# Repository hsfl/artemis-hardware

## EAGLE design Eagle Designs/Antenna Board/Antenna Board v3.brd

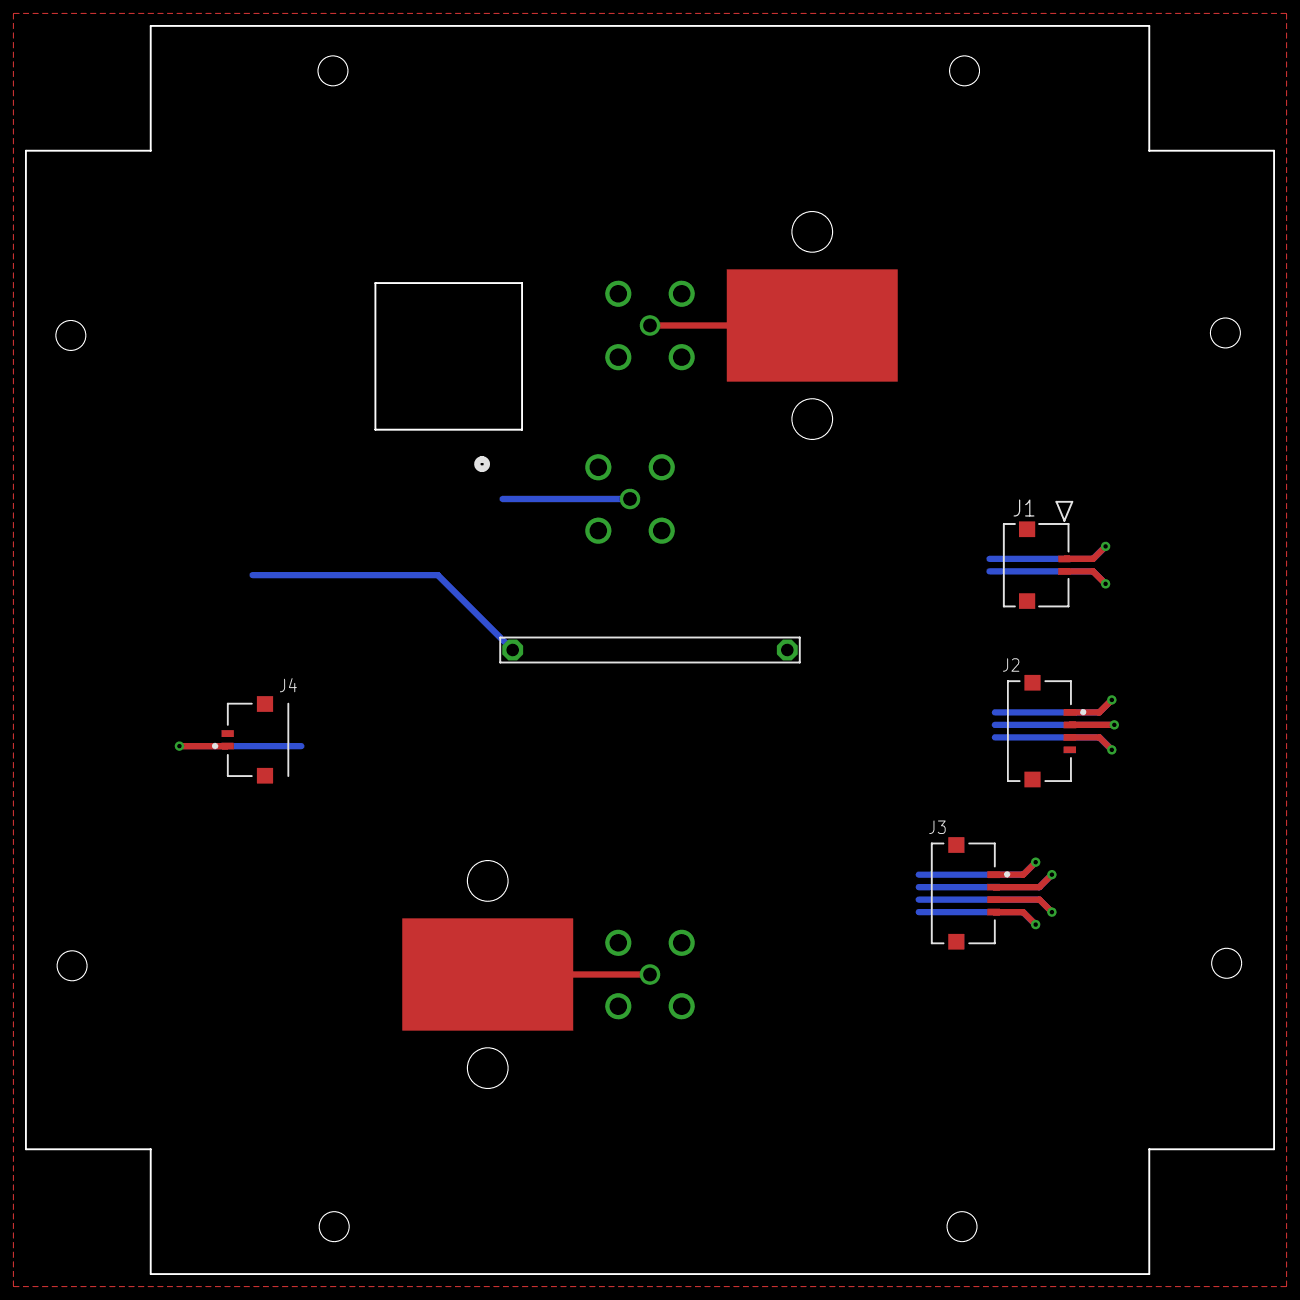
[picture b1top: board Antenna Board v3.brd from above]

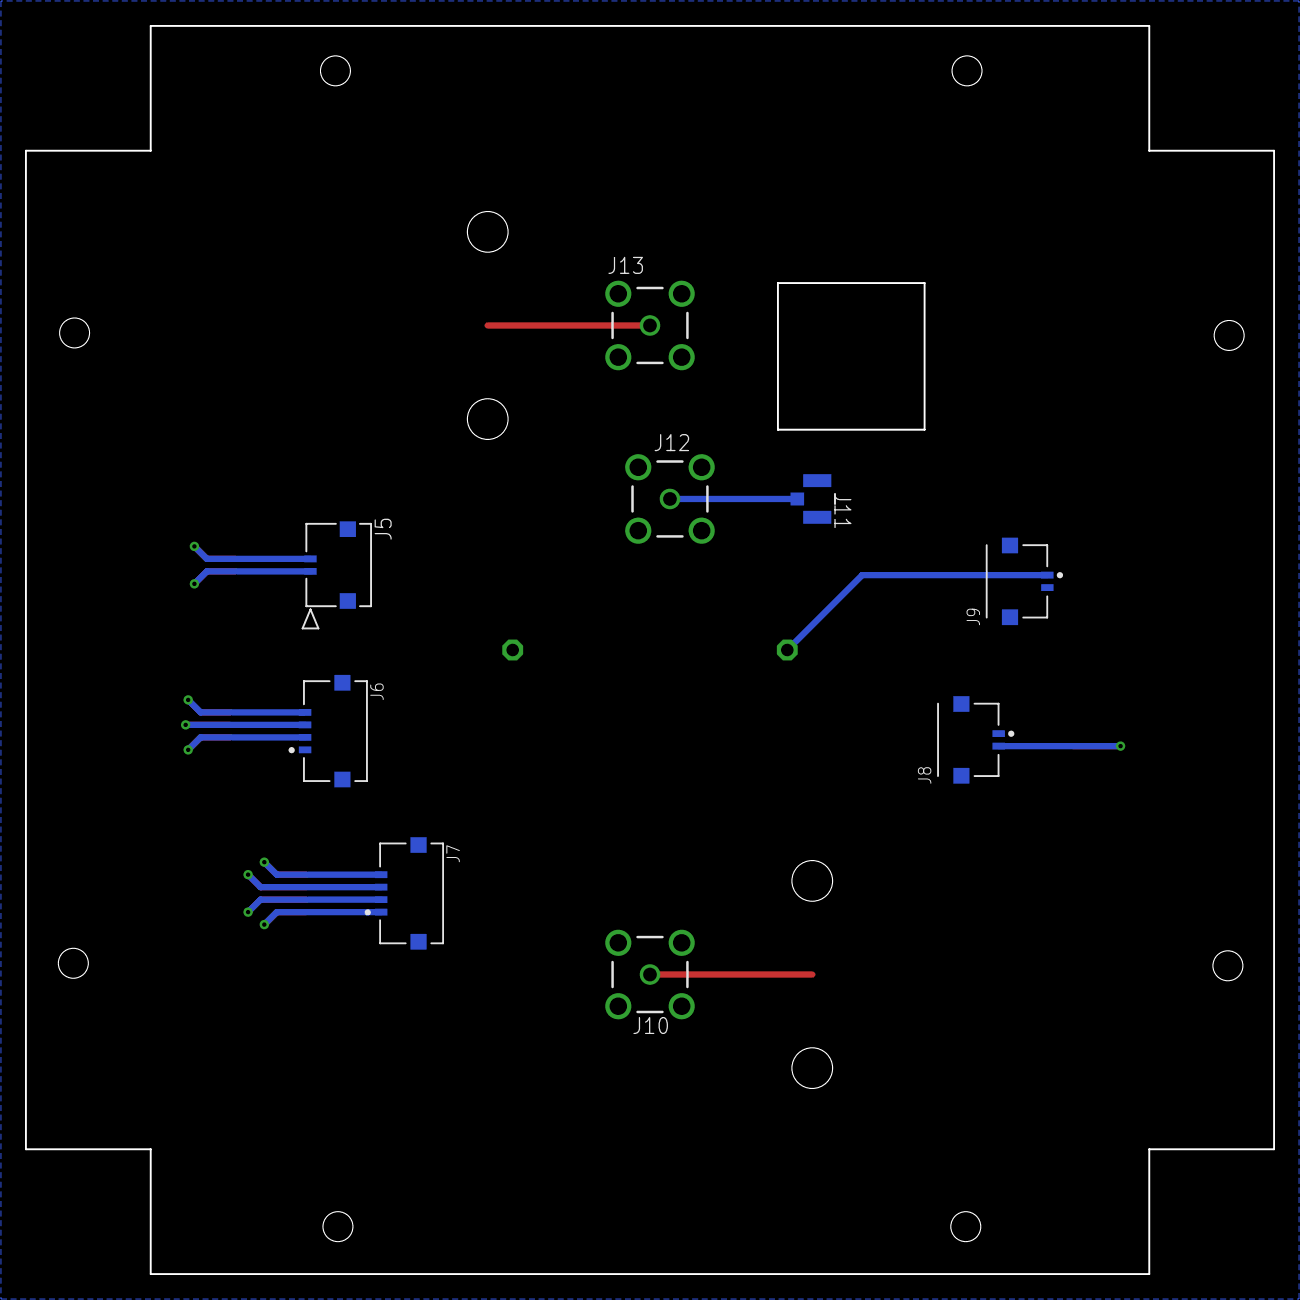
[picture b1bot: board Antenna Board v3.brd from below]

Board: 2 copper layers, 100.0 x 100.0 mm, 16 parts (9 on the bottom side), 15 nets.

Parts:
J1, J5: 5037630291; CON_5037630291
J2, J3, J6, J7: MOLEX_503763-0491MOLEX_503763-0491_0_0; MOLEX_503763-0491_0
J4, J8, J9: MOLEX_503763-0291MOLEX_503763-0291_0_0; MOLEX_503763-0291_0
J10, J12, J13: MCX-J-P-X-ST-TH1; SAMTEC_MCX-J-P-X-ST-TH1
J11: U.FL-R-SMT-1(01); CONN_-SMT-1(01)
U$1, U$2: ANTENNA_PAD
U$3: BURNWIRE

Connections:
ANTENNA1: J10.1, U$2.1
ANTENNA2: J13.1, U$1.1
GND: J1.3, J1.4, J2.4, J2.5, J2.6, J3.5, J3.6, J4.2, J4.3, J4.4, J5.3, J5.4, J6.1, J6.5, J6.6, J7.5, J7.6, J8.1, J8.3, J8.4, J9.2, J9.3, J9.4, J10.S1, J10.S2, J10.S3, J10.S4, J11.1, J11.2, J12.S1, J12.S2, J12.S3, J12.S4, J13.S1, J13.S2, J13.S3, J13.S4, U$3.2
ORION-SPACE: J11.3, J12.1
RBF1: J1.1, J5.2
RBF2: J1.2, J5.1
RX+: J3.1, J7.4
RX-: J3.2, J7.3
TCK: J2.3, J6.2
TMS: J2.2, J6.3
TX+: J3.3, J7.2
TX-: J3.4, J7.1
VCC_BATT: J4.1, J8.2
VCC_BURN: J9.1, U$3.1
VRTREF: J2.1, J6.4

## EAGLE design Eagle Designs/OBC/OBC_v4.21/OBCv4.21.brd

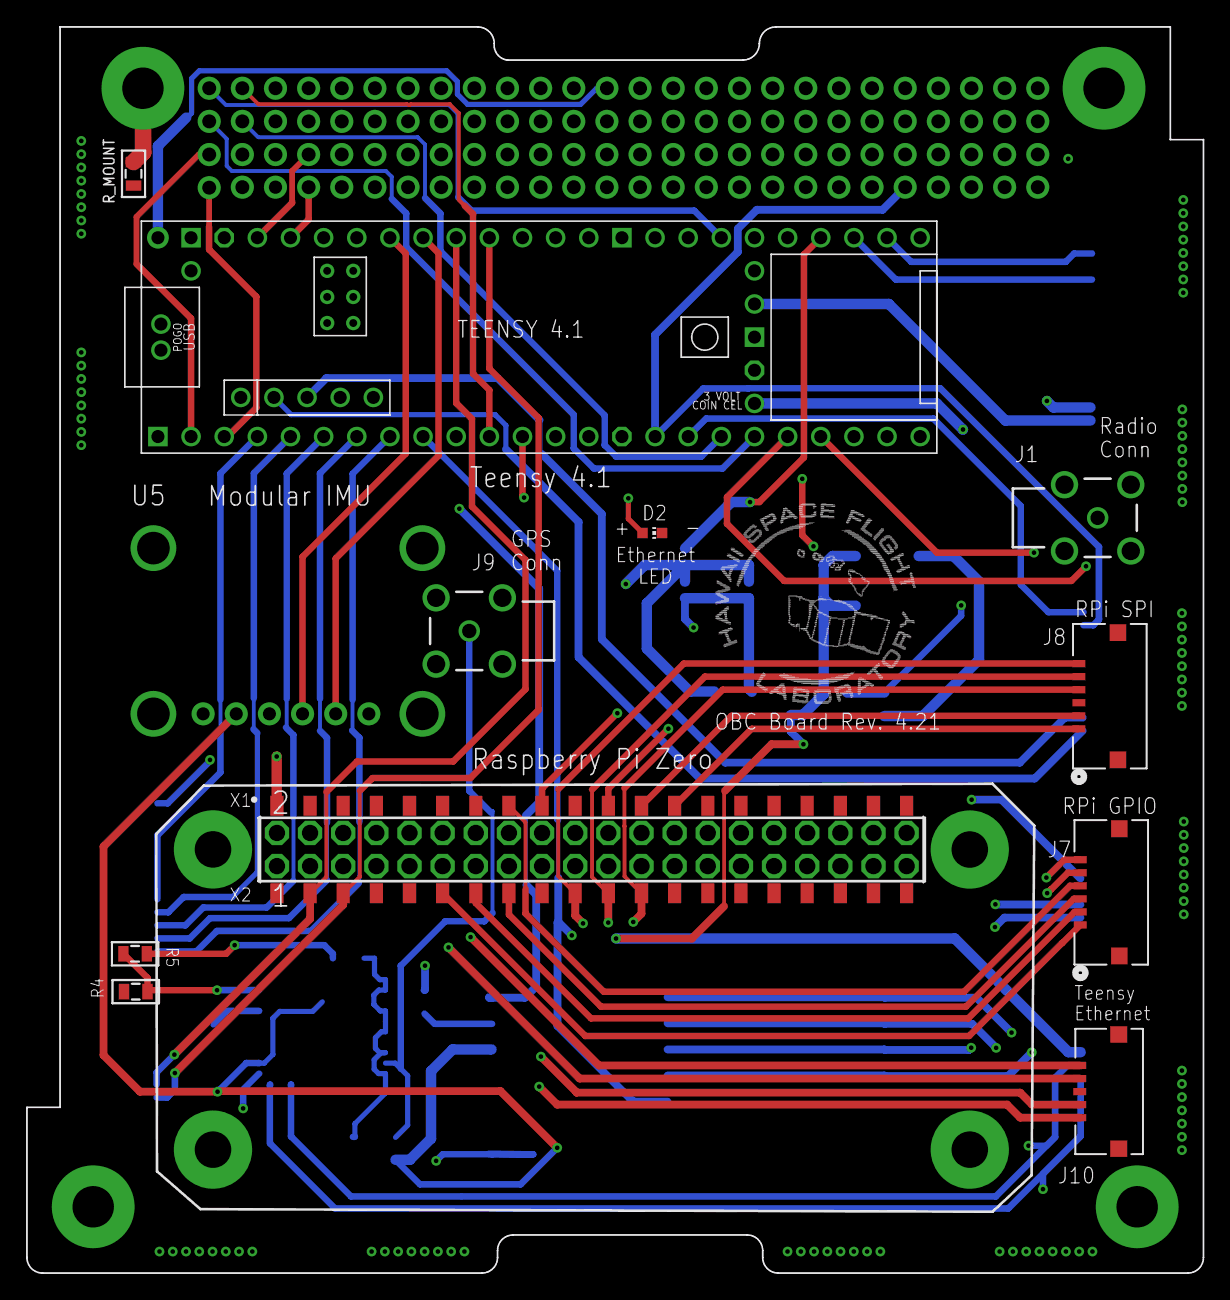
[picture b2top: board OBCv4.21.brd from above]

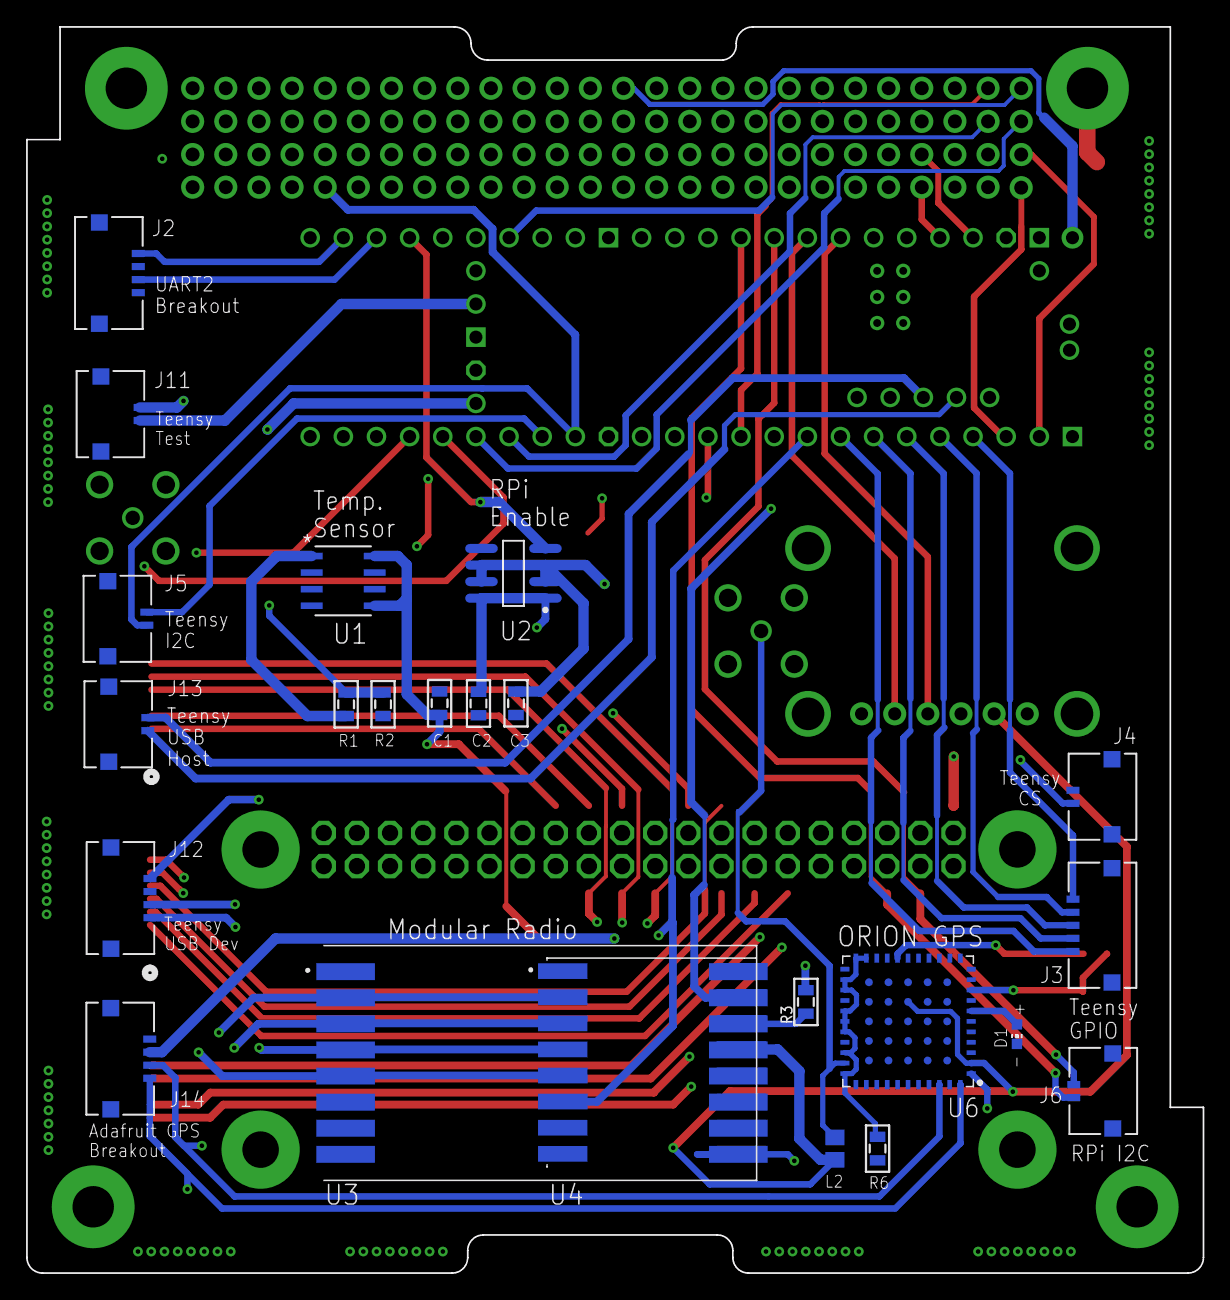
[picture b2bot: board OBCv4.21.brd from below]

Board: 4 copper layers, 90.2 x 95.5 mm, 37 parts (23 on the bottom side), 70 nets.

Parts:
C1: 0.1 uF; 0805
C2, C3: 1 uF; 0805
D1, D2: CHIP-LED0603
H1: PC104_WCONN
J1, J9: MCX-J-P-H-RA-TH1; SAMTEC_MCX-J-P-H-RA-TH1
J2, J12, J14: 5037630491; CON_5037630491
J3, J10: 5037630591; CON_5037630591
J4, J5, J6, J11, J13: 5037630291; CON_5037630291
J7: 503763-0691; CONN_503763-0691_MOL
J8: 5037630691; CONN_503763-0691_MOL
L2: AIMC-0805-2N2S-T; INDC2012X105N
R1: 45.3k; 0805
R2: 10k; 0805
R3, R4, R5, R6: 0; 0805
R_MOUNT: 1M; 0805
U1: TMP36FSZR_8_ADI-L; R_8_ADI-L
U2: LTC1477CS8LINEAR_TECHNOLOGY_LTC1477CS8_0_2; LINEAR_TECHNOLOGY_LTC1477CS8_2
U3: RFM23BP
U4: RFM69HCW
U5: 1X06_ROUND_70
U6: ORION_A38LORION_A38L; ORION_A38L
U$1: TEENSY41
X1: C25582-40G-M36-0A; ADAFRUIT_C25582-40G-M36-0A_0
X2: SSW-120-02-G-D

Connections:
3V3_BUS: H1.2.27, H1.2.28, R5.1, U6.18
5V_BUS: C3.1, H1.2.25, H1.2.26, U2.2, U2.3, U2.6, U2.7, U$1.+5V, U$1.VIN
+3V3_VCC: C1.1, J14.2, L2.1, U1.5, U1.8, U3.13, U4.13, U5.2, U6.2, U6.58, U$1.3V3-1, U$1.3V3-2, U$1.3V3-3
AIN0: R1.1, R2.2, U$1.14-A0/TX3/SPDIF_OUT
AIN1: H1.1.3, U$1.15-A1/RX3/SPDIF_IN
AIN2: H1.1.4, U$1.41-A17/MISO1
AIN3: H1.1.5, U$1.20-A6/TX5/LRCLK1
AIN4: H1.1.6, U$1.21-A7/RX5/BCLK1
AIN5: H1.1.7, U$1.22-A8/CTX1
AIN6: H1.1.8, U$1.23-A9/CRX1/MCLK1
ANT_CONN: J1.1, U3.9, U4.9
DIO1: U3.15, U4.15, U$1.8-TX2/IN1
ETH_RX+: J10.1, U$1.R+
ETH_RX-: J10.2, U$1.R-
ETH_TX+: J10.5, U$1.T+
ETH_TX-: J10.4, U$1.T-
GND: C1.2, C2.2, C3.2, D1.C, D2.C, H1.2.7, H1.2.14, H1.2.17, H1.2.21, H1.2.22, H1.2.29, H1.2.30, H1.2.32, H1.2.47, H1.2.48, J1.S1, J1.S2, J1.S3, J1.S4, J2.2, J2.4, J2.5, J2.6, J3.6, J3.7, J4.2, J4.3, J4.4, J5.3, J5.4, J6.3, J6.4, J7.7, J7.8, J8.3, J9.S1, J9.S2, J9.S3, J9.S4, J10.3, J10.6, J10.7, J11.3, J11.4, J12.2, J12.5, J12.6, J13.3, J13.4, J14.1, J14.5, J14.6, R2.1, R4.1, R6.2, R_MOUNT.2, U1.4, U2.5, U3.1, U3.8, U3.10, U4.1, U4.8, U4.10, U5.3, U6.10, U6.11, U6.15, U6.19, U6.64, U$1.G, U$1.GND1, U$1.GND2, U$1.GND3, U$1.GND4, U$1.GND5, U$1.GND6, X1.39
GPIO17: J7.1, X1.11
GPIO22: J7.3, X1.15
GPIO23: J7.4, X1.16
GPIO24: J7.5, X1.18
GPIO25: J7.6, X1.22
GPIO27: J7.2, X1.13
GPS_RSTN: U6.1, U$1.33-MCLK2
I2C1_SCL: H1.1.43, J5.2, U$1.24-A10/TX6/SCL2
I2C1_SDA: H1.1.41, J5.1, U$1.25-A11/RX6/SDA2
I2C2_SCL: U5.4, U$1.19-A5/SCL0
I2C2_SDA: U5.5, U$1.18-A4/SDA0
unnamed: D2.A, U$1.LED
unnamed: R3.1, U3.14
unnamed: R1.2, U1.1
unnamed: R4.2, R5.2, U6.9
unnamed: J9.1, L2.2, U6.32
unnamed: D1.A, U6.7
unnamed: H1.P$4, R_MOUNT.1
RADIO_RESET: R3.2, U4.6, U$1.7-RX2/OUT1A
RF_GND: R6.1, U6.21, U6.22, U6.24, U6.25, U6.27, U6.28, U6.29, U6.31, U6.33
RPI_5V_PWR_IN: C2.1, U2.1, U2.8, X1.2
RPI_ENABLE: U2.4, U$1.36-PWM
SCL1_I2C: J6.1, U$1.16-A2/RX4/SCL1, X1.5
SDA1_I2C: J6.2, U$1.17-A3/TX4/SDA1, X1.3
SPI0_CE0_N: J8.2, X1.24
SPI0_CE1_N: J8.1, X1.26
SPI0_MISO: J8.5, U$1.12-MISO/MQSL, X1.21
SPI0_MOSI: J8.6, U$1.11-MOSI/CTX1, X1.19
SPI0_SCLK: J8.4, U$1.13-SCK/LED, X1.23
SPI1_CS1: U3.5, U4.5, U$1.38-A14/CS/IN1
SPI1_D0: H1.2.2, U3.2, U4.2, U$1.39-A15/CS/OUT1A
SPI1_D1: H1.2.3, U3.3, U4.3, U$1.26-A12/MOSI1
SPI1_SCLK: H1.2.1, U3.4, U4.4, U$1.27-A13/SCK1
T_CS: J4.1, U$1.10-CS\MQSR
T_CS1: H1.2.4, U$1.9-OUT1C
T_GPIO2: J3.5, U$1.2-OUT2
T_GPIO3: J3.4, U$1.3-LRCLK2
T_GPIO4: J3.3, U$1.4-BCLK2
T_GPIO5: J3.2, U$1.5-IN2
T_GPIO6: J3.1, U$1.6-OUT1D
T_PROGRAM: J11.2, U$1.PROGRAM
T_VBAT: J11.1, U$1.VBAT
T_VUSB: J12.1, U$1.VUSB
UART2_RXD: J2.1, U$1.34-RX8
UART2_TXD: J2.3, U$1.35-TX8
UART4_RXD: H1.1.2, U$1.0-RX1/CS1/CRX2
UART4_TXD: H1.1.1, U$1.1-TX1/MISO1/CTX2
UART5_RXD: J14.3, U6.42, U$1.29-TX7
UART5_TXD: J14.4, U6.44, U$1.28-RX7
USB_DEV_D+: J12.4, U$1.D+
USB_DEV_D-: J12.3, U$1.D-
USB_HOST_D+: J13.1, U$1.DP
USB_HOST_D-: J13.2, U$1.DM

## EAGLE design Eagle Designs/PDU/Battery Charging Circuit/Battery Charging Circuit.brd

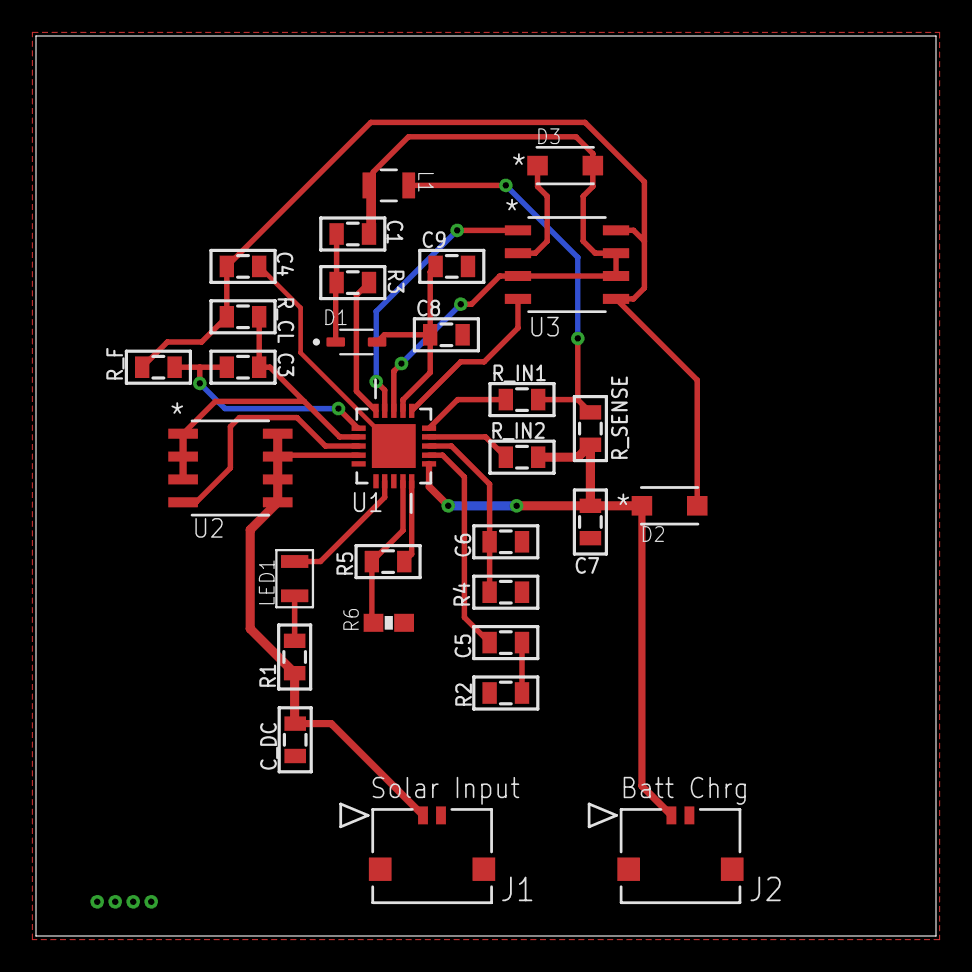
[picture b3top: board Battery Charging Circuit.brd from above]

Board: 2 copper layers, 50.0 x 50.0 mm, 30 parts (0 on the bottom side), 24 nets.

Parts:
C1, C3, C5: 0.1 uF; 0805
C4, C7: 10 uF; 0805
C6: 4.7 uF; 0805
C8, C9: 1 uF; 0805
C_DC: 0.1 uF; 0805
D1: CMDSH-3TR; SOD2512X110N
D2, D3: MBR230S1F; CR_0LSFT1G_ONS
J1, J2: 5037630291; CON_5037630291
L1: AIML-0805-150K-T; AIML-0805_ABR
LED1: LED_0805
R1: 3 k; 0805
R2: 6.04 k; 0805
R3: 0; 0805
R4: 26.7 k; 0805
R5: 169 k; 0805
R6: 28.4k; 0603-RES
R_CL: 1; 0805
R_F: 5.1 k; 0805
R_IN1, R_IN2: 3.01 k; 0805
R_SENSE: 1; 0805
U1: LTC4012IUFPBF; QFN50P400X400X80-21N
U2: SI4431BDY-T1-E3; SOIC-8_SI
U3: AO4818B; SOIC8_NARROW_VIS

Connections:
BATT_CHRG: C7.1, D2.1, J2.1, R_IN2.2, R_SENSE.1, U1.11
BGATE: U1.16, U3.4
CHRG: LED1.2, U1.7
GND: C4.2, C6.2, C7.2, C8.2, C9.2, C_DC.2, J1.2, J1.3, J1.4, J2.2, J2.3, J2.4, R2.1, R4.1, R6.1, U1.21
INFET: U1.3, U2.4
INH_SW1_NC: C_DC.1, J1.1, R1.2, U1.4, U2.5, U2.6, U2.7, U2.8
ITH: C5.1, U1.12
unnamed: LED1.1, R1.1
unnamed: C5.2, R2.2
unnamed: R3.1, U1.20
unnamed: C3.2, R_F.1, U1.1
unnamed: C8.1, C9.1, D1.A, U1.17
unnamed: C1.1, D1.C, R3.2
unnamed: R_IN1.1, U1.15
unnamed: R_IN2.1, U1.14
unnamed: C6.1, R4.2, U1.13
unnamed: R5.1, U1.10
unnamed: R5.2, R6.2, U1.9
R_SENSE_R_IN1: L1.1, R_IN1.2, R_SENSE.2
S2: D3.1, U3.2
SW: C1.2, D3.2, L1.2, U1.18, U3.3, U3.6, U3.7
TGATE: U1.19, U3.1
U2_S: C3.1, R_CL.1, U1.2, U2.1, U2.2, U2.3
VBATT: C4.1, D2.2, R_CL.2, R_F.2, U3.5, U3.8

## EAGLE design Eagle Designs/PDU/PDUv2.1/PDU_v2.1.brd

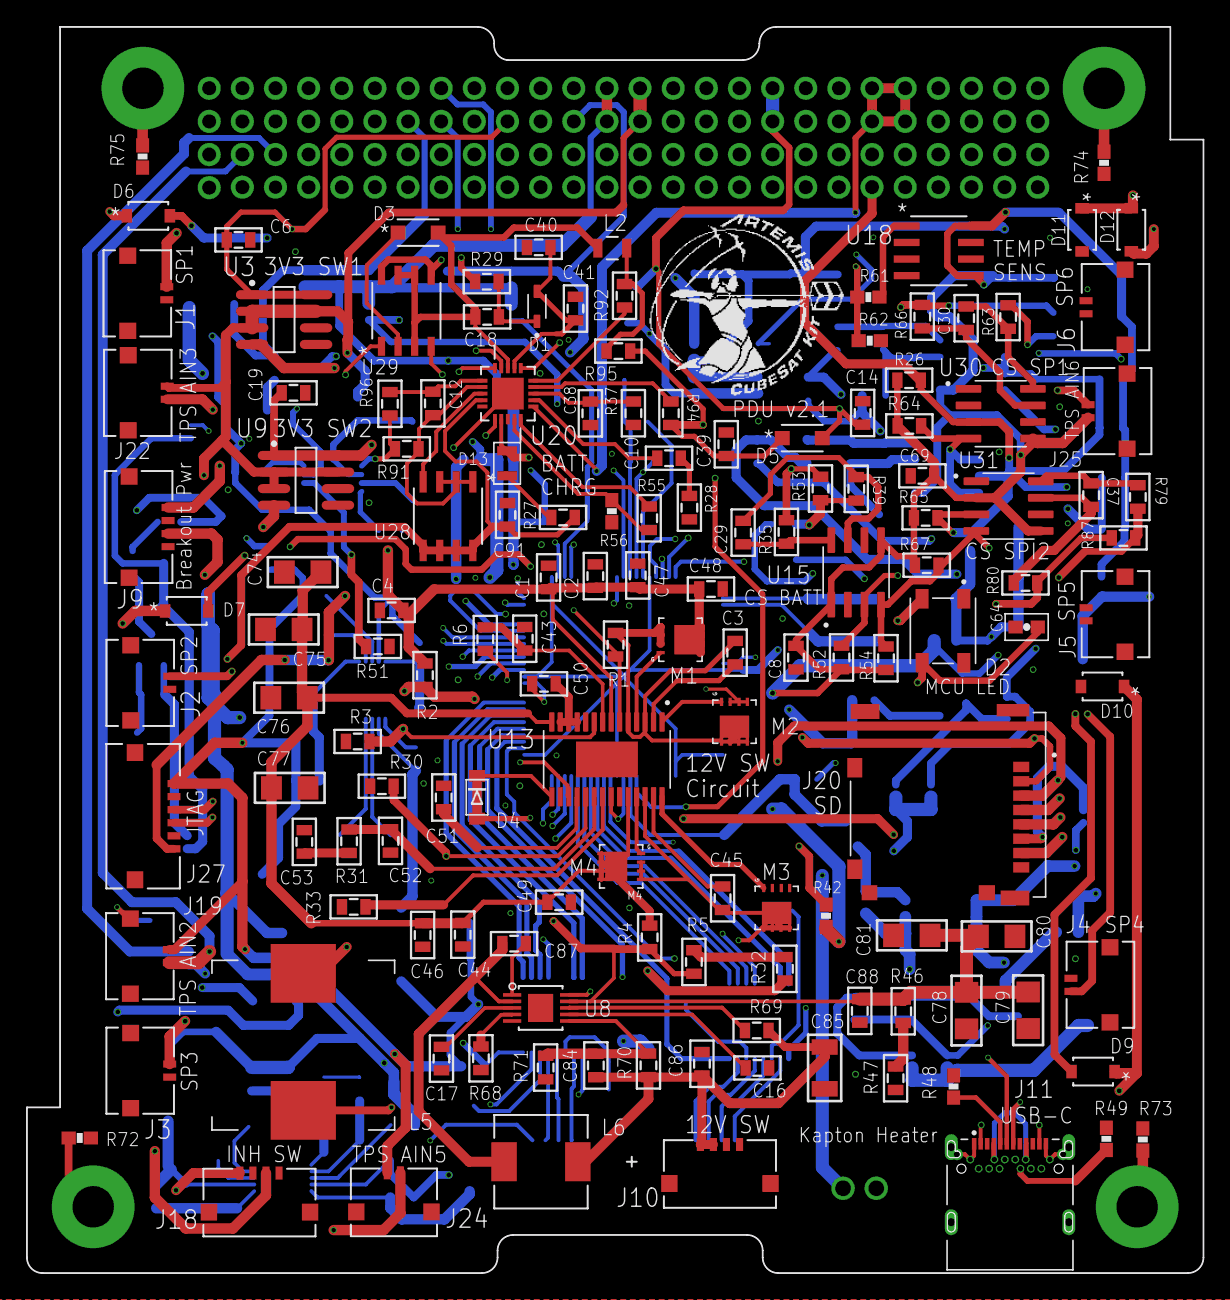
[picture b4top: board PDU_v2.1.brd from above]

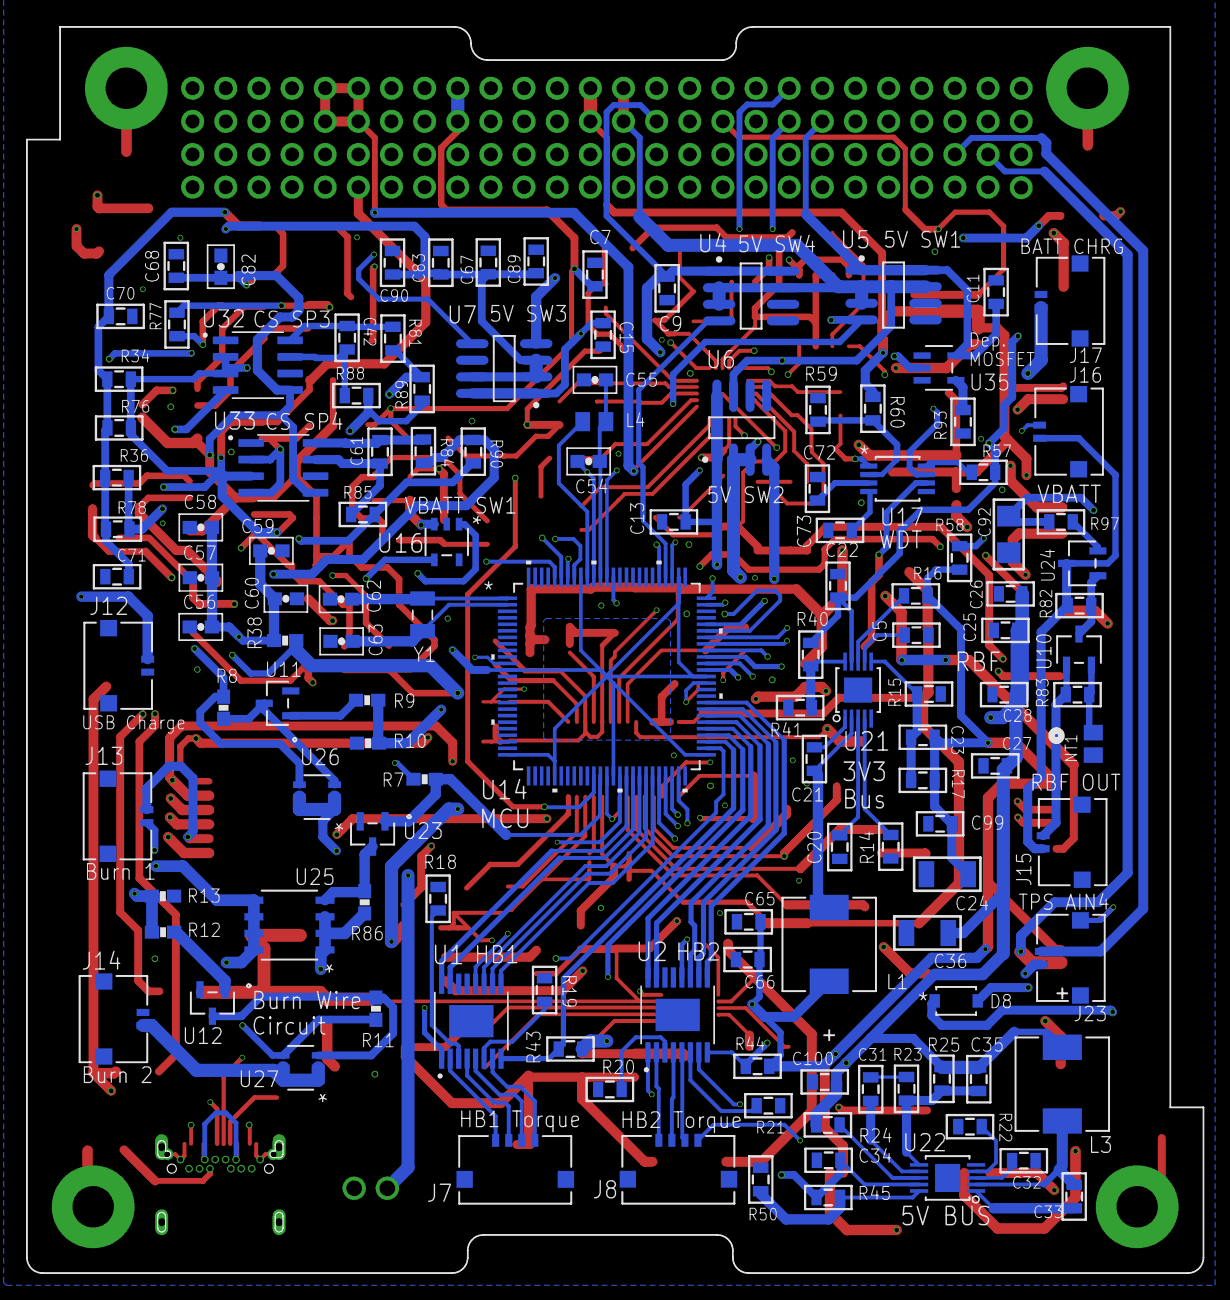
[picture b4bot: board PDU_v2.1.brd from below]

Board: 4 copper layers, 90.2 x 95.5 mm, 276 parts (130 on the bottom side), 190 nets.

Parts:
C1, C2: 22 uF; 0805
C3, C5, C7, C8, C10, C12, C16, C18, C21, C25, C27, C29, C30, C31, C33, C37, C42, C45, C51, C61, C65, C66, C67, C68, C69, C70, C71, C72, C83, C87, C89, C90, C91: 0.1 uF; 0805
C4, C6, C9, C11, C13, C15, C17, C19, C20, C32, C40, C41, C44, C73: 1 uF; 0805
C14, C26, C28, C39, C46, C49: 10 uF; 0805
C22, C34, C38, C43, C47, C48, C86, C88, C99, C100: 4.7 uF; 0805
C23, C35, C84: 10 pF; 0805
C24, C36, C85: 47 uF; 1210
C50: 0.47 uF; 0805
C52: 100 pF; 0805
C53: 4.7 nF; 0805
C54, C56: 10 uF; 0603-CAP
C55, C57, C58: 1 uF; 0603-CAP
C59, C60, C64, C82: 0.1 uF; 0603-CAP
C62, C63: 22 pF; 0603-CAP
C74, C75, C76, C77, C78, C79, C80, C81: 33 uF; 1206
C92: 1 uF; 1206
D1: CMDSH-3TR; SOD2512X110N
D2: 1655; LED_1655
D3, D5: MBR230S1F; CR_0LSFT1G_ONS
D4: SOD-123FL
D6, D7, D8, D9, D10, D11, D12: PMEG10020ELRX; CFP3_SOD123W_NEX
D13: LED_0805
H1: PC104_WCONN
J1, J2, J3, J4, J5, J6, J12, J13, J14, J15, J16, J17, J19, J22, J23, J24, J25: 5037630291; CON_5037630291
J7, J8, J9, J10, J18: 5037630491; CON_5037630491
J11: UJ31-CH-G1-SMT-TR; CUI_UJ31-CH-G1-SMT-TR
J20: 503182-1852; MOLEX_503182-1852
J27: 5037630691; CONN_503763-0691_MOL
J28: 68016-202HLF
L1, L3, L6: PA4341.222NLT; IND_222NLT_PUL
L2: AIML-0805-150K-T; AIML-0805_ABR
L4: 10 uH; INDC2012X100N
L5: 6 uH; 7443551600
M1, M2: BSZ100N06LS3
M3, M4: BSZ033NE2LS5; BSZ100N06LS3
NT1: AIMC-0805-2N2S-T; INDC2012X105N
R1: 4 m; 0805
R2: 390 k; 0805
R3: 180 k; 0805
R4: 15 m; 0805
R5: 130 k; 0805
R6, R33, R59, R69: 100 k; 0805
R7, R10, R13, R38, R42, R62, R86: 10 k; 0603-RES
R8, R11: 100 k; 0603-RES
R9, R12: 4.7 k; 0603-RES
R14, R22: 18.2 k; 0805
R15: 309 k; 0805
R16, R24: 47 k; 0805
R17, R25, R41, R50, R70, R82, R83: 1 M; 0805
R18, R19, R20, R21: 330 m; 0805
R23: 187 k; 0805
R26, R34, R36, R43, R44, R52, R54, R64, R65, R67, R76, R78: 3.3 k; 0805
R27: 3 k; 0805
R28: 6.04 k; 0805
R29, R40, R45, R58: 0; 0805
R30, R32, R51, R57, R93: 10 k; 0805
R31: 27 k; 0805
R35, R39, R63, R66, R79, R80, R81, R84, R85, R88: 10; 0805
R37: 26.7 k; 0805
R46: 510 k; 0805
R47: 270 k; 0805
R48, R49: 5.1 k; 0603-RES
R53, R77, R87, R89, R90: 2 m; 0805
R55: 169 k; 0805
R56: 28.4k; 0603-RES
R60: 63.4 k; 0805
R61: 45.3 k; 0603-RES
R68: 40.2 k; 0805
R71: 69.8 k; 0805
R72, R73, R74, R75: 1 M; 0603-RES
R91, R95: 1; 0805
R92, R94: 3.01 k; 0805
R96: 5.1 k; 0805
R97: 16; 0805
U1, U2: DRV8847PWPR; SOP65P640X120-17N
U3, U4, U5, U6, U7, U9: LTC1477CS8LINEAR_TECHNOLOGY_LTC1477CS8_0_2; LINEAR_TECHNOLOGY_LTC1477CS8_2
U8, U21, U22: LT8609A; MSOP-10_MSE
U10, U24: AO3404A; SOT-23-3L_AOS
U11, U12: IRLML2803PBFCT-ND; PG-TO23-3_INF
U13: LT8390EFE#PBF; SOP65P640X120-29N
U14: ATSAME51N19A-AF; TQFP100_14X14MC_MCH
U15, U30, U31, U32, U33: INA219BIDR; SOIC127P599X175-8N
U16: MIC2514YM5-TR; SOT-23-5_M5_MCH
U17: MAX16998AAUA+T; 21-0036K_MXM
U18: TMP36FSZ; R_8_ADI
U20: LTC4012IUFPBF; QFN50P400X400X80-21N
U23: BC848ALT1G; SOT-23_ONS
U25: SI4835DDY-T1-GE3; SOIC_DY-T1-GE3_VIS
U26, U27: SI3493DDV-T1-GE3; 6TSOP_VIS
U28: SI4431BDY-T1-E3; SOIC-8_SI
U29: AO4818B; SOIC8_NARROW_VIS
U35: LND01K1-G; SOT-23-5_MC_MCH
Y1: ABS07-32.768KHZ-T; XTAL_ABS07-32.768KHZ-T

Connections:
5V_BURN: R7.2, U14.37, U23.1
5V_USB_CHRG: D12.2, J12.1
12V_OUT: C78.1, C79.1, C80.1, C81.1, C88.1, D4.A, D4.C, R4.2, R5.2, R46.1, U8.9, U13.15
12V_SW1: C84.2, C85.1, C86.1, J10.1, J10.2, L6.1, R69.2, R70.2
AIN1: H1.1.3, R61.1, R62.2
AIN2: H1.1.4, J19.2
AIN3: H1.1.5, J22.2
AIN4: H1.1.6, J23.2
AIN5: H1.1.7, J24.2
AIN6: H1.1.8, J25.2
BATT_CHRG: C39.1, D5.1, H1.2.41, H1.2.42, H1.2.43, H1.2.44, J17.1, R94.2, R95.1, U20.11
BGATE: U20.16, U29.4
BST_3V3_BUS: C87.1, U8.1
BURN1_EN: R9.2, R10.1, U14.96
BURN2_EN: R12.2, R13.1, U14.49
BUS_3V3: C8.1, C23.2, C24.1, C65.1, C66.1, C68.1, C69.1, C70.1, C71.1, C82.2, C99.1, H1.2.27, H1.2.28, J19.1, J20.4, J22.1, J23.1, J24.1, J25.1, J27.1, L1.1, R16.2, R17.2, R26.1, R34.1, R36.1, R38.2, R42.2, R43.1, R44.1, R52.1, R54.1, R58.2, R60.2, R64.1, R65.1, R67.1, R76.1, R78.1, U3.2, U3.3, U3.7, U9.2, U9.3, U9.7, U15.1, U15.5, U18.5, U18.8, U30.5, U31.2, U31.5, U32.5, U33.5
BUS_3V3_FB: C23.1, R15.2, R17.1, U21.6
BUS_3V3_PG: R16.1, U21.8
BUS_3V3_TRSS: C5.1, U21.7
BUS_3V3_VIN_EN: R40.1, R41.2, U21.10
BUS_5V: C25.2, C26.2, C27.2, C28.2, C35.2, C36.1, C64.1, C67.1, C83.1, C89.1, C90.1, C100.1, D2.3, H1.2.25, H1.2.26, L3.1, R24.2, R25.2, U1.12, U2.12, U4.2, U4.3, U4.7, U5.2, U5.3, U5.7, U6.2, U6.3, U6.7, U7.2, U7.3, U7.7
BUS_5V_FB: C35.1, R23.2, R25.1, U22.6
BUS_5V_PG: R24.1, U22.8
BUS_5V_TRSS: C31.1, U22.7
BUS_5V_VIN_EN: R45.1, R50.2, U22.10
CCO_0: C62.2, U14.1, Y1.2
CCO_1: C63.2, U14.2, Y1.1
CHRG: D13.2, U14.70, U20.7
CS_SOL1_VIN+: C30.1, R63.1, U30.8
CS_SOL1_VIN-: C30.2, R66.1, U30.7
CS_SOL2_VIN+: C37.1, R79.1, U31.8
CS_SOL2_VIN-: C37.2, R80.1, U31.7
CS_SOL3_VIN+: C42.1, R81.1, U32.8
CS_SOL3_VIN-: C42.2, R88.1, U32.7
CS_SOL4_VIN+: C61.1, R84.1, U33.8
CS_SOL4_VIN-: C61.2, R85.1, U33.7
CS_VBATT: C92.1, R35.2, R53.2, R97.2
CS_VBATT_VIN+: C29.1, R35.1, U15.8
CS_VBATT_VIN-: C29.2, R39.1, U15.7
FAULT1: R43.2, U1.8, U14.53
FAULT2: R44.2, U2.8, U14.52
FB_3V3_BUS: C84.1, R70.1, R71.2, U8.6
GND: C1.2, C2.2, C4.2, C5.2, C6.2, C7.2, C8.2, C9.2, C11.2, C13.2, C14.2, C15.2, C16.2, C17.2, C19.2, C20.2, C22.2, C24.2, C25.1, C26.1, C27.1, C28.1, C31.2, C32.2, C34.2, C36.2, C38.2, C39.2, C40.2, C41.2, C43.2, C44.2, C46.2, C47.2, C48.2, C49.2, C50.2, C51.2, C52.2, C53.2, C54.2, C55.2, C56.2, C57.2, C58.2, C59.2, C60.2, C62.1, C63.1, C64.2, C65.2, C66.2, C67.2, C68.2, C69.2, C70.2, C71.2, C72.1, C73.2, C74.2, C75.2, C76.2, C77.2, C78.2, C79.2, C80.2, C81.2, C82.1, C83.2, C85.2, C86.2, C88.2, C89.2, C90.2, C91.2, C92.2, C99.2, C100.2, D2.1, H1.2.7, H1.2.9, H1.2.14, H1.2.17, H1.2.21, H1.2.22, H1.2.29, H1.2.30, H1.2.32, H1.2.47, H1.2.48, J1.2, J1.3, J1.4, J2.2, J2.3, J2.4, J3.2, J3.3, J3.4, J4.2, J4.3, J4.4, J5.2, J5.3, J5.4, J6.2, J6.3, J6.4, J7.5, J7.6, J8.5, J8.6, J9.2, J9.4, J9.5, J9.6, J10.3, J10.4, J10.5, J10.6, J11.A1, J11.A12, J11.B1, J11.B12, J11.SH1, J11.SH2, J11.SH3, J11.SH4, J11.SH5, J11.SH6, J12.2, J12.3, J12.4, J13.1, J13.3, J13.4, J14.1, J14.3, J14.4, J15.3, J15.4, J16.2, J16.3, J16.4, J17.2, J17.3, J17.4, J18.2, J18.4, J18.5, J18.6, J19.3, J19.4, J20.6, J20.P1, J20.P2, J20.P3, J20.P4, J20.P5, J22.3, J22.4, J23.3, J23.4, J24.3, J24.4, J25.3, J25.4, J27.2, J27.5, J28.2, M2.P$2, M2.P$3, M2.P$4, M3.P$2, M3.P$3, M3.P$4, NT1.1, R3.1, R7.1, R10.2, R13.2, R14.1, R15.1, R18.1, R19.1, R20.1, R21.1, R22.1, R23.1, R28.1, R30.1, R33.1, R37.1, R41.1, R47.1, R48.1, R49.1, R50.1, R51.1, R56.1, R59.1, R62.1, R68.1, R71.1, R72.1, R73.1, R74.1, R75.1, R93.2, U1.13, U2.13, U3.5, U4.5, U5.5, U6.5, U7.5, U8.5, U8.11, U9.5, U11.2, U12.2, U13.10, U13.22, U13.29, U14.11, U14.24, U14.31, U14.38, U14.50, U14.62, U14.76, U14.90, U15.2, U15.6, U16.2, U17.5, U18.4, U20.21, U21.5, U21.11, U22.5, U22.11, U23.2, U30.1, U30.2, U30.6, U31.1, U31.6, U32.1, U32.6, U33.1, U33.6
I2C1_SCL: H1.1.43, R36.2, R54.2, R64.2, R67.2, R78.2, U15.4, U30.4, U31.4, U32.4, U33.2, U33.4
I2C1_SDA: H1.1.41, R26.2, R34.2, R52.2, R65.2, R76.2, U15.3, U30.3, U31.3, U32.2, U32.3, U33.3
IN1: U1.16, U14.41
IN2: U1.15, U14.42
IN3: U1.9, U14.45
IN4: U1.10, U14.44
IN5: U2.16, U14.55
IN6: U2.15, U14.56
IN7: U2.9, U14.59
IN8: U2.10, U14.58
INFET: U20.3, U28.4
INH_SW1_COM: D6.1, D7.1, D8.1, D9.1, D10.1, D11.1, D12.1, J18.1
INH_SW1_NC: C91.1, J18.3, R27.2, U20.4, U28.5, U28.6, U28.7, U28.8
ITH: C10.1, U20.12
LED: D2.2, U14.71
unnamed: C3.1, M1.P$2, M1.P$3, M1.P$4, M2.P$5, M2.P$6, M2.P$7, M2.P$8, M2.P$9, R1.2, U13.3, U13.5
unnamed: C3.2, U13.2
unnamed: M2.P$1, U13.1
unnamed: M1.P$1, U13.4
unnamed: M3.P$1, U13.28
unnamed: C20.1, U21.3
unnamed: R14.2, U21.4
unnamed: C21.1, U21.1
unnamed: C21.2, L1.2, U21.2
unnamed: R8.2, R11.2, U25.5, U25.6, U25.7, U25.8, U26.4, U27.4
unnamed: R12.1, U12.1
unnamed: R11.1, U12.3, U27.3
unnamed: R86.1, U23.3, U25.4
unnamed: R9.1, U11.1
unnamed: R8.1, U11.3, U26.3
unnamed: R82.1, U10.3, U24.1
unnamed: R19.2, U1.6
unnamed: R18.2, U1.3
unnamed: R21.2, U2.6
unnamed: R20.2, U2.3
unnamed: R22.2, U22.4
unnamed: D13.1, R27.1
unnamed: C32.1, U22.3
unnamed: C33.1, U22.1
unnamed: C33.2, L3.2, U22.2
unnamed: C10.2, R28.2
unnamed: C12.2, R96.1, U20.1
unnamed: R29.1, U20.20
unnamed: C40.1, C41.1, D1.A, U20.17
unnamed: C52.1, R31.2, U13.20
unnamed: C18.1, D1.C, R29.2
unnamed: R5.1, R32.2
unnamed: C45.1, L5.P$2, M3.P$5, M3.P$6, M3.P$7, M3.P$8, M3.P$9, M4.P$2, M4.P$3, M4.P$4, U13.26
unnamed: R61.2, U18.1
unnamed: R92.1, U20.15
unnamed: C43.1, R6.2, U13.8
unnamed: L5.P$1, R1.1, U13.6
unnamed: L4.2, U14.91
unnamed: C45.2, U13.27
unnamed: C44.1, C46.1, C49.1, C74.1, C75.1, C76.1, C77.1, M4.P$5, M4.P$6, M4.P$7, M4.P$8, M4.P$9, R4.1, U13.14, U13.24
unnamed: M4.P$1, U13.25
unnamed: C51.1, U13.18
unnamed: R94.1, U20.14
unnamed: R33.2, U13.21
unnamed: C38.1, R37.2, U20.13
unnamed: R55.1, U20.10
unnamed: C53.1, R31.1
unnamed: R55.2, R56.2, U20.9
unnamed: C54.1, C55.1, L4.1, U14.89
unnamed: H1.P$1, R72.2
unnamed: R93.1, U35.4
unnamed: H1.P$4, R75.2
unnamed: C72.2, U17.3
unnamed: H1.P$2, R73.2
unnamed: C73.1, U17.4
unnamed: R59.2, R60.1, U17.2
unnamed: H1.P$3, R74.2
PG_3V3_BUS: R69.1, U8.8
POST_RBF_VBATT: R97.1, U24.2
PY_VBATT: J15.1, J16.1, R82.2, U24.3
RBF_GND: NT1.2, R83.2, U10.2
RBF_SW: J15.2, R83.1, U10.1
RESET: H1.1.52, J27.6, R58.1, U14.88, U17.7
RT_3V3_BUS: R68.2, U8.4
R_SENSE_R_IN1: L2.1, R92.2, R95.2
S2: D3.1, U29.2
SD_CS: H1.2.49, J20.2, R42.1, U14.87
SD_MISO: H1.2.52, J20.7, U14.48
SD_MOSI: H1.2.51, J20.3, U14.46
SD_SCK: H1.2.50, J20.5, U14.47
SHDN: U14.36, U20.6
SLEEP1: U1.1, U14.40
SLEEP2: U2.1, U14.54
SOLAR_IN1: J1.1, R63.2, R77.2
SOLAR_IN1_LOAD: D6.2, R66.2, R77.1
SOLAR_IN2: J2.1, R79.2, R87.2
SOLAR_IN2_LOAD: D7.2, R80.2, R87.1
SOLAR_IN3: J3.1, R81.2, R89.2
SOLAR_IN3_LOAD: D8.2, R88.2, R89.1
SOLAR_IN4: J4.1, R84.2, R90.2
SOLAR_IN4_LOAD: D9.2, R85.2, R90.1
SW: C18.2, D3.2, L2.2, U20.18, U29.3, U29.6, U29.7
SWCLK: J27.4, U14.93
SWDIO: J27.3, U14.94
SW_3V3_1: C6.1, H1.2.19, J9.1, U3.1, U3.8
SW_3V3_2: C19.1, H1.2.20, U9.1, U9.8
SW_3V3_BUS: C87.2, L6.2, U8.2
SW_3V3_EN1: U3.4, U14.64
SW_3V3_EN2: U9.4, U14.65
SW_5V_1: C11.1, H1.2.13, U5.1, U5.8, U35.5
SW_5V_2: C13.1, H1.2.15, J28.1, U6.1, U6.8
SW_5V_3: C15.1, H1.2.16, J9.3, U7.1, U7.8
SW_5V_4: C1.1, C2.1, C4.1, C9.1, C47.1, C48.1, H1.2.23, M1.P$5, M1.P$6, M1.P$7, M1.P$8, M1.P$9, R2.2, U4.1, U4.8, U13.7
SW_5V_EN1: U5.4, U14.67, U35.2
SW_5V_EN2: U6.4, U14.66
SW_5V_EN3: U7.4, U14.78
SW_5V_EN4: U4.4, U14.79
SW_12V_EN1: R2.1, R3.2, U8.10, U13.9
SW_12V_FB: R30.2, R32.1, U13.19
SW_12V_IN1: C50.1, U13.11, U13.12, U13.13
SW_12V_PGOOD: R6.1, U13.17
SW_VBATT: H1.2.45, H1.2.46, U16.4
SW_VBATT_EN: U14.80, U16.1
TGATE: U20.19, U29.1
TORQUE_1A: J7.1, U1.2
TORQUE_1B: J7.2, U1.4
TORQUE_2A: J7.4, U1.7
TORQUE_2B: J7.3, U1.5
TORQUE_3A: J8.1, U2.2
TORQUE_3B: J8.2, U2.4
TORQUE_4A: J8.4, U2.7
TORQUE_4B: J8.3, U2.5
TRQ1: U1.11, U14.43
TRQ2: U2.11, U14.57
TRSS_3V3_BUS: C16.1, U8.7
U2_S: C12.1, R91.1, U20.2, U28.1, U28.2, U28.3
UART2_RXD: H1.1.1, J11.A2, U14.69
UART2_TXD: H1.1.2, J11.A11, U14.68
USB_CC1: J11.A5, R48.2
USB_CC2: J11.B5, R49.2
USB_D+: J11.A6, J11.B6, U14.75
USB_D-: J11.A7, J11.B7, U14.74
VBATT: C7.1, C14.1, C22.1, C34.1, D5.2, H1.2.35, H1.2.36, R39.2, R40.2, R45.2, R53.1, R57.2, R86.2, R91.2, R96.2, U16.3, U17.1, U21.9, U22.9, U25.1, U25.2, U25.3, U29.5, U29.8
VBURN1: J13.2, U26.1, U26.2, U26.5, U26.6
VBURN2: J14.2, U27.1, U27.2, U27.5, U27.6
VBUS: J11.A4, J11.A9, J11.B4, J11.B9
VCC_3V3_BUS: C17.1, U8.3
VDD: C56.1, C57.1, C58.1, C59.1, C60.1, R38.1, U14.12, U14.25, U14.30, U14.39, U14.51, U14.63, U14.77, U14.92
VIN3: U3.6, U4.6, U5.6, U6.6, U7.6, U9.6
V_BATT_SENSE: R46.2, R47.2
WDT_EN: R57.1, U17.8
WDT_WDI: R51.2, U14.95, U17.6

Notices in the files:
parts and their libraries:
COPYRIGHT: Copyright (C) 2018 Accelerated Designs. All rights reserved
microbuilder: This work is placed in the public domain, and may be freely used for commercial and non-commercial work with the following conditions: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
COPYRIGHT: Copyright (C) 2021 Ultra Librarian. All rights reserved.
